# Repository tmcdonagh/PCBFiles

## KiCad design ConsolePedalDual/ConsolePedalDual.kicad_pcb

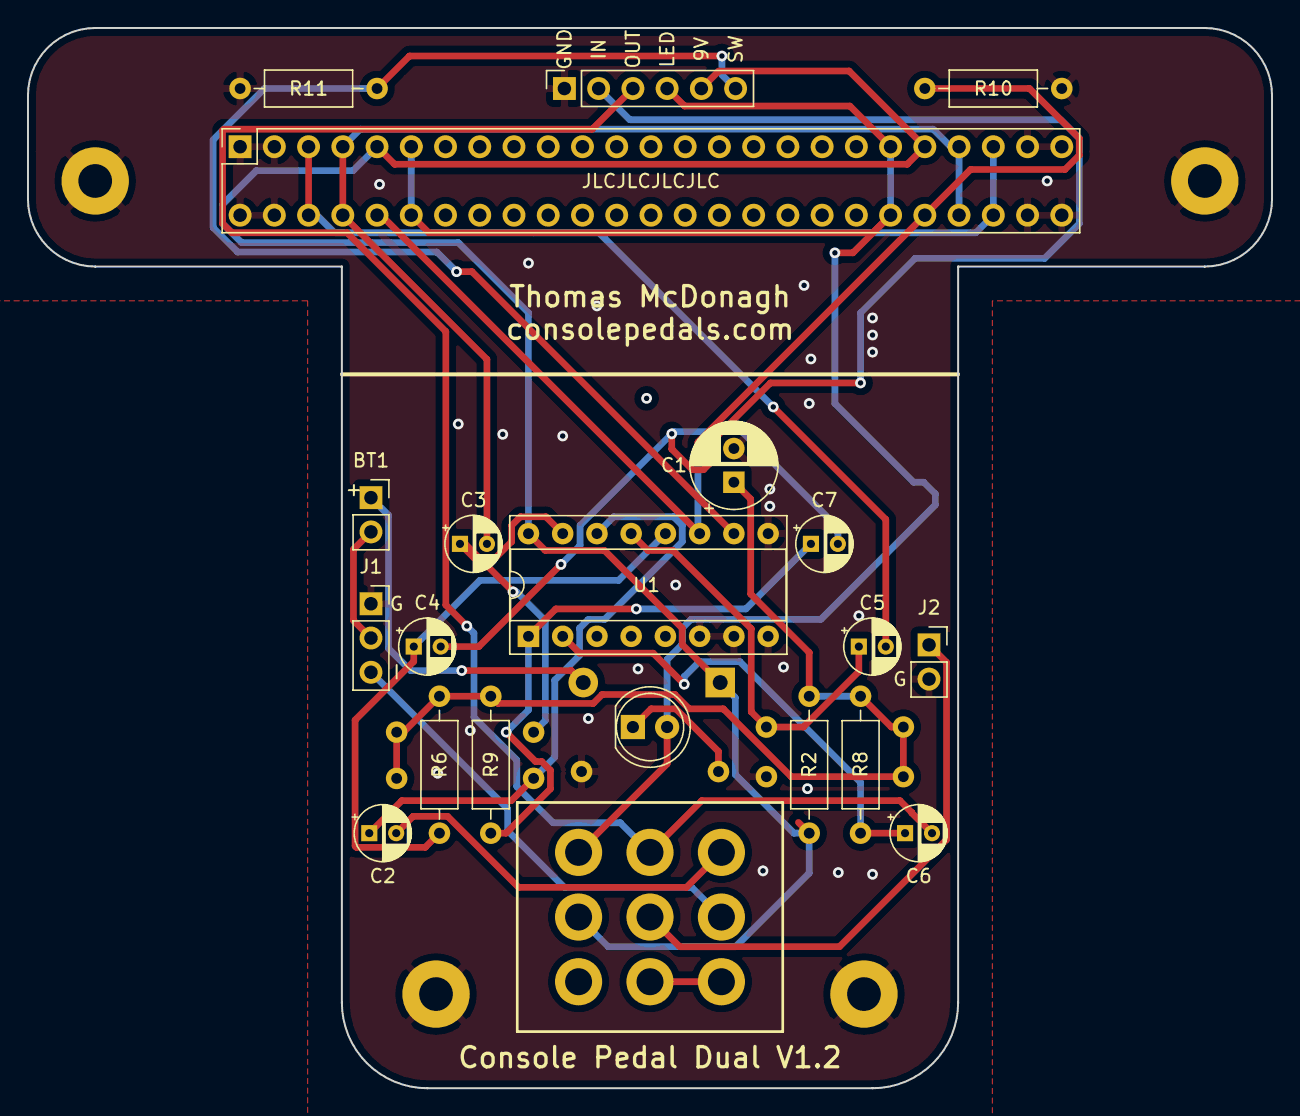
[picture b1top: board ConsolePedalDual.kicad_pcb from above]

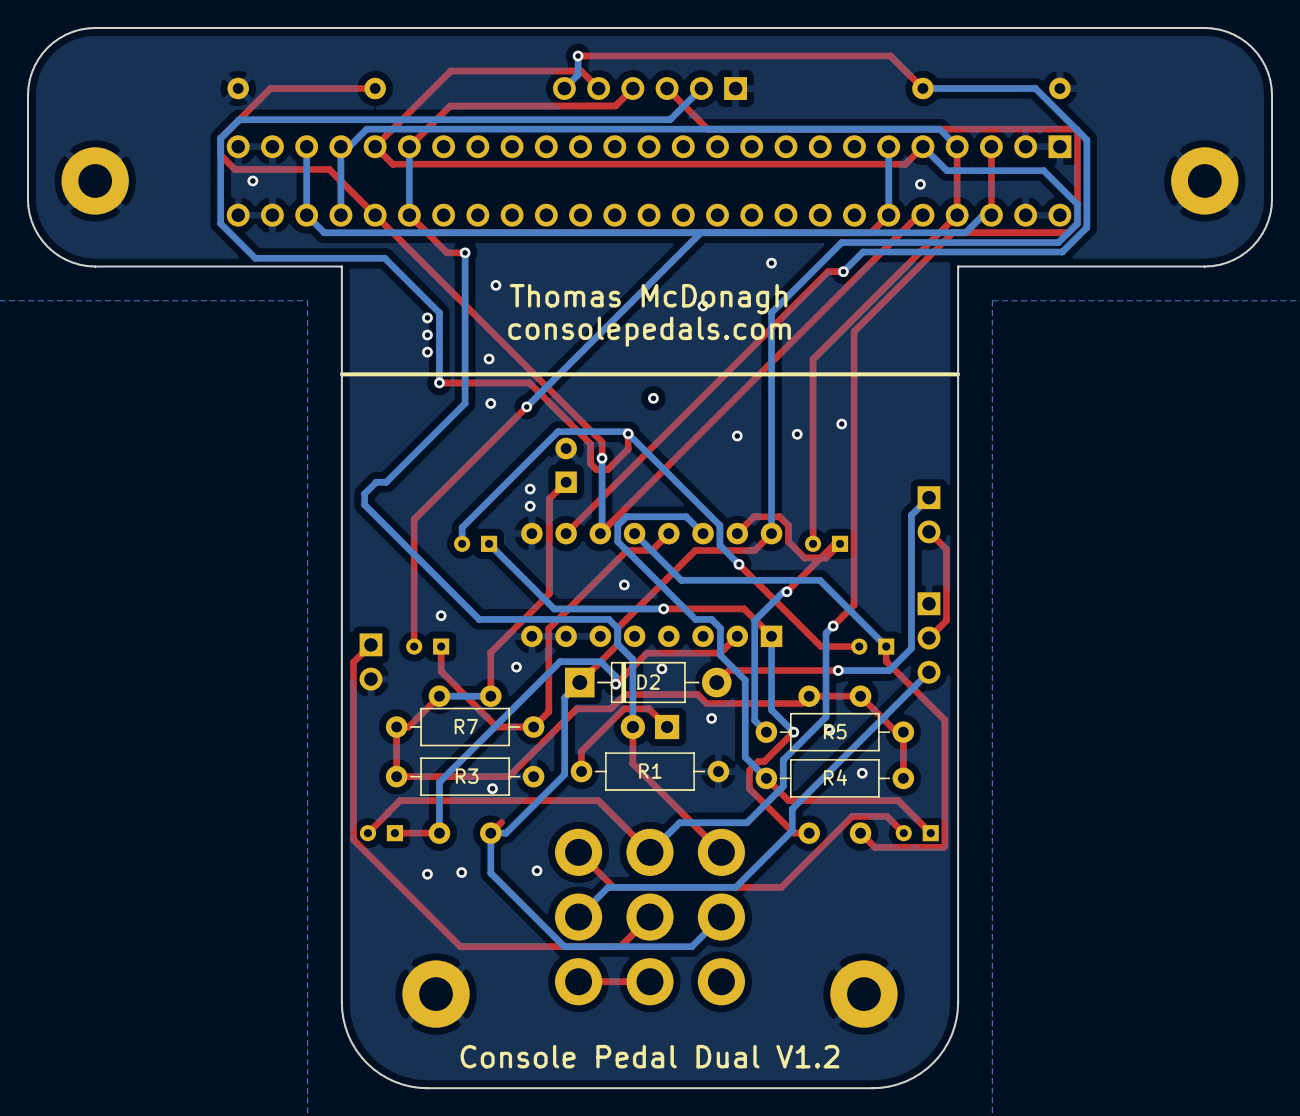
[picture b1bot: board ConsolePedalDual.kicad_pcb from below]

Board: 2 copper layers, 92.3 x 78.7 mm, 31 parts (6 on the bottom side), 23 nets.

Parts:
BT1: Battery; PinSocket_1x02_P2.54mm_Vertical
C1: 47uF; CP_Radial_D6.3mm_P2.50mm
C2, C3, C4, C5, C6, C7: 2.2uF; CP_Radial_D4.0mm_P2.00mm
D1: LED; LED_D5.0mm
D2: D; D_DO-41_SOD81_P10.16mm_Horizontal
H1, H2, H3, H4: Mount; MountingHole_2.5mm_Pad
J1: AudioJack3; PinSocket_1x03_P2.54mm_Vertical
J2: AudioJack2; PinSocket_1x02_P2.54mm_Vertical
J3: Slot A; n64Socket
J4: Slot B; PinSocket_1x06_P2.54mm_Vertical
R1: LED; R_Axial_DIN0207_L6.3mm_D2.5mm_P10.16mm_Horizontal
R2, R3: 10K; R_Axial_DIN0207_L6.3mm_D2.5mm_P10.16mm_Horizontal
R4, R5, R6, R7, R8, R9: 510K; R_Axial_DIN0207_L6.3mm_D2.5mm_P10.16mm_Horizontal
R10, R11: 3M; R_Axial_DIN0207_L6.3mm_D2.5mm_P10.16mm_Horizontal
S1: SWITCH-3PDT-PTH-STOMP; STOMP_SWITCH_3PDT
U1: CD4053B; DIP-16_W7.62mm_Socket

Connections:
+9V: D2.1, J3.9, J3.41, J4.5, R2.1, S1.P$8, U1.16
/Input: C2.2, S1.P$3
/LEDPower: D1.2, J3.11, J3.12, J3.39, J3.40, J4.4, S1.P$9
/Output: C6.2, J4.3, S1.P$6
/SlotA: J3.10, J3.42, R10.2, U1.11
/SlotAInput: C5.2, J3.5, J3.6, J3.45, J3.46
/SlotAOutput: C3.2, J3.7, J3.8, J3.43, J3.44
/SlotB: J4.6, R11.1, U1.10
/SlotBInput: C4.2, C7.2, J4.2
/VREF: C1.1, R2.2, R3.1, R4.2, R5.2, R6.1, R7.2, R8.1, R9.2
GND: C1.2, H1.1, H2.1, H3.1, H4.1, J1.1, J2.2, J3.1, J3.2, J3.3, J3.4, J3.47, J3.48, J3.49, J3.50, J4.1, R1.2, R3.2, R10.1, R11.2, U1.6, U1.7, U1.8, U1.9
unnamed: BT1.1, D2.2
unnamed: BT1.2, J1.2
unnamed: C2.1, R4.1, U1.14
unnamed: C3.1, R5.1, U1.15
unnamed: C4.1, R6.2, U1.12
unnamed: C5.1, R7.1, U1.13
unnamed: C6.1, R8.2, U1.2
unnamed: C7.1, R9.1, U1.1
unnamed: D1.1, R1.1
unnamed: J1.3, S1.P$2
unnamed: J2.1, S1.P$5
unnamed: S1.P$1, S1.P$4

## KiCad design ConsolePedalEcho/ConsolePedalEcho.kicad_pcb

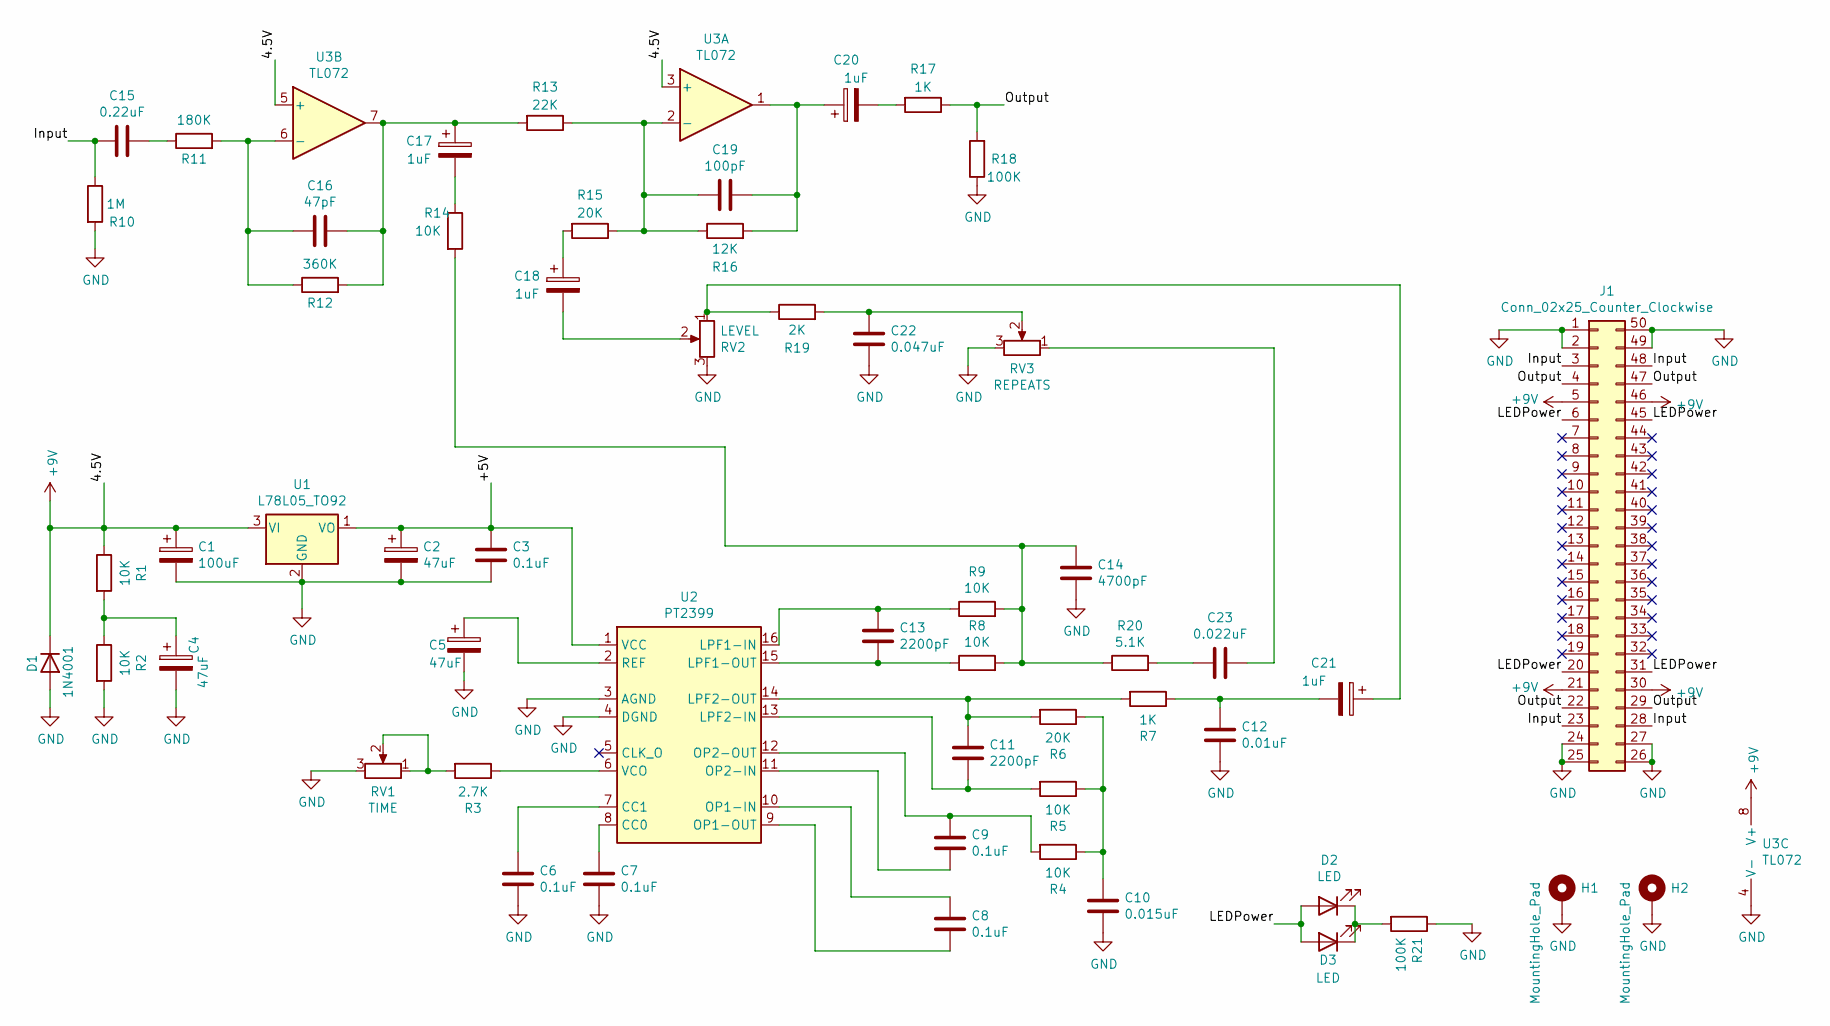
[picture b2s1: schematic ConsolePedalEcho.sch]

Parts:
C1: 100uF; CP_Radial_D8.0mm_P3.50mm
C2, C4, C5: 47uF; CP_Radial_D5.0mm_P2.00mm
C3, C6, C7, C8, C9: 0.1uF; C_Rect_L7.2mm_W2.5mm_P5.00mm_FKS2_FKP2_MKS2_MKP2
C10: 0.015uF; C_Rect_L7.2mm_W2.5mm_P5.00mm_FKS2_FKP2_MKS2_MKP2
C11, C13: 2200pF; C_Rect_L7.2mm_W2.5mm_P5.00mm_FKS2_FKP2_MKS2_MKP2
C12: 0.01uF; C_Rect_L7.2mm_W2.5mm_P5.00mm_FKS2_FKP2_MKS2_MKP2
C14: 4700pF; C_Rect_L7.2mm_W2.5mm_P5.00mm_FKS2_FKP2_MKS2_MKP2
C15: 0.22uF; C_Rect_L7.2mm_W2.5mm_P5.00mm_FKS2_FKP2_MKS2_MKP2
C16: 47pF; C_Axial_L3.8mm_D2.6mm_P7.50mm_Horizontal
C17, C18, C20, C21: 1uF; CP_Radial_D5.0mm_P2.00mm
C19: 100pF; C_Axial_L3.8mm_D2.6mm_P7.50mm_Horizontal
C22: 0.047uF; C_Rect_L7.2mm_W2.5mm_P5.00mm_FKS2_FKP2_MKS2_MKP2
C23: 0.022uF; C_Rect_L7.2mm_W2.5mm_P5.00mm_FKS2_FKP2_MKS2_MKP2
D1: 1N4001; D_DO-41_SOD81_P10.16mm_Horizontal
D2, D3: LED; LED_D5.0mm
H1, H2: MountingHole_Pad; MountingHole_2.5mm_Pad
J1: Conn_02x25_Counter_Clockwise; N64-Connector
R1, R2, R4, R5, R8, R9, R14: 10K; R_Axial_DIN0207_L6.3mm_D2.5mm_P10.16mm_Horizontal
R3: 2.7K; R_Axial_DIN0207_L6.3mm_D2.5mm_P10.16mm_Horizontal
R6, R15: 20K; R_Axial_DIN0207_L6.3mm_D2.5mm_P10.16mm_Horizontal
R7, R17: 1K; R_Axial_DIN0207_L6.3mm_D2.5mm_P10.16mm_Horizontal
R10: 1M; R_Axial_DIN0207_L6.3mm_D2.5mm_P10.16mm_Horizontal
R11: 180K; R_Axial_DIN0207_L6.3mm_D2.5mm_P10.16mm_Horizontal
R12: 360K; R_Axial_DIN0207_L6.3mm_D2.5mm_P10.16mm_Horizontal
R13: 22K; R_Axial_DIN0207_L6.3mm_D2.5mm_P10.16mm_Horizontal
R16: 12K; R_Axial_DIN0207_L6.3mm_D2.5mm_P10.16mm_Horizontal
R18, R21: 100K; R_Axial_DIN0207_L6.3mm_D2.5mm_P10.16mm_Horizontal
R19: 2K; R_Axial_DIN0207_L6.3mm_D2.5mm_P10.16mm_Horizontal
R20: 5.1K; R_Axial_DIN0207_L6.3mm_D2.5mm_P10.16mm_Horizontal
RV1: TIME; Potentiometer_Bourns_PTV09A-1_Single_Vertical
RV2: LEVEL; Potentiometer_Bourns_PTV09A-1_Single_Vertical
RV3: REPEATS; Potentiometer_Bourns_PTV09A-1_Single_Vertical
U1: L78L05_TO92; TO-92_Inline
U2: PT2399; DIP-16_W7.62mm_Socket
U3: TL072; DIP-8_W7.62mm_Socket

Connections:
+9V: C1.1, D1.1 (K), J1.5, J1.21, J1.30, J1.46, R1.1, U1.3 (VI), U3.3 (+), U3.5 (+), U3.8 (V+)
/+5V: C2.1, C3.1, U1.1 (VO), U2.1 (VCC)
/Input: C15.2, J1.3, J1.23, J1.28, J1.48, R10.1
/LEDPower: D2.2 (A), D3.2 (A), J1.6, J1.20, J1.31, J1.45
/Output: J1.4, J1.22, J1.29, J1.47, R17.1, R18.2
GND: C1.2, C2.2, C3.2, C4.2, C5.2, C6.2, C7.2, C10.2, C12.2, C14.2, C22.1, D1.2 (A), H1.1, H2.1, J1.1, J1.2, J1.24, J1.25, J1.26, J1.27, J1.49, J1.50, R2.2, R10.2, R18.1, R21.1, RV1.3, RV2.3, RV3.3, U1.2 (GND), U2.3 (AGND), U2.4 (DGND), U3.4 (V-)
unnamed: C4.1, R1.2, R2.1
unnamed: C5.1, U2.2 (REF)
unnamed: C6.1, U2.7 (CC1)
unnamed: C7.1, U2.8 (CC0)
unnamed: C8.1, U2.10 (OP1-IN)
unnamed: C8.2, U2.9 (OP1-OUT)
unnamed: C9.1, R4.2, U2.12 (OP2-OUT)
unnamed: C9.2, U2.11 (OP2-IN)
unnamed: C10.1, R4.1, R5.1, R6.1
unnamed: C11.1, R6.2, R7.2, U2.14 (LPF2-OUT)
unnamed: C11.2, R5.2, U2.13 (LPF2-IN)
unnamed: C12.1, C21.2, R7.1
unnamed: C13.1, R9.1, U2.16 (LPF1-IN)
unnamed: C13.2, R8.1, U2.15 (LPF1-OUT)
unnamed: C14.1, R8.2, R9.2, R14.2, R20.1
unnamed: C15.1, R11.1
unnamed: C16.1, C17.1, R12.2, R13.2, U3.7
unnamed: C16.2, R11.2, R12.1, U3.6 (-)
unnamed: C17.2, R14.1
unnamed: C18.1, R15.2
unnamed: C18.2, RV2.2
unnamed: C19.1, C20.1, R16.2, U3.1
unnamed: C19.2, R13.1, R15.1, R16.1, U3.2 (-)
unnamed: C20.2, R17.2
unnamed: C21.1, R19.1, RV2.1
unnamed: C22.2, R19.2, RV3.2
unnamed: C23.1, R20.2
unnamed: C23.2, RV3.1
unnamed: D2.1 (K), D3.1 (K), R21.2
unnamed: R3.1, U2.6 (VCO)
unnamed: R3.2, RV1.1, RV1.2

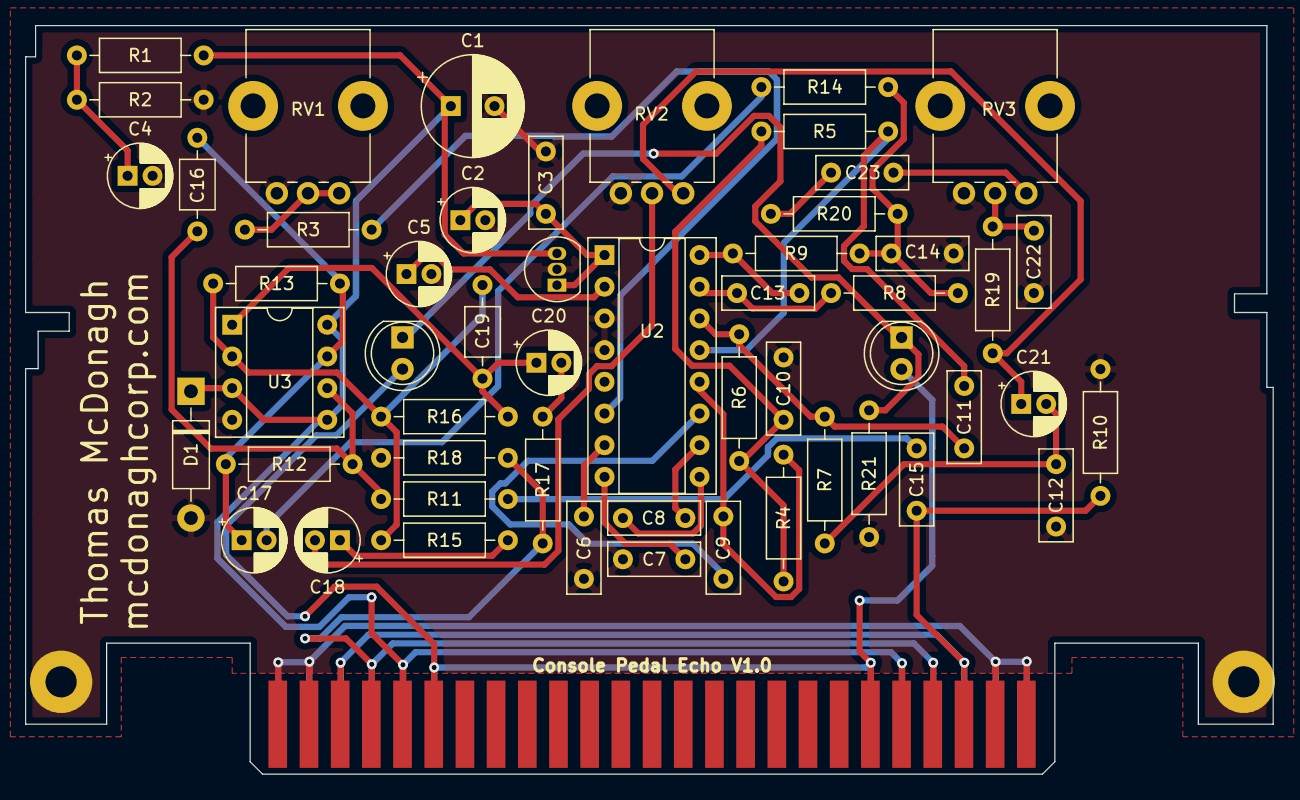
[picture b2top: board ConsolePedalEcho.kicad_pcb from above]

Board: 2 copper layers, 100.0 x 60.0 mm, 56 parts (0 on the bottom side), 37 nets.

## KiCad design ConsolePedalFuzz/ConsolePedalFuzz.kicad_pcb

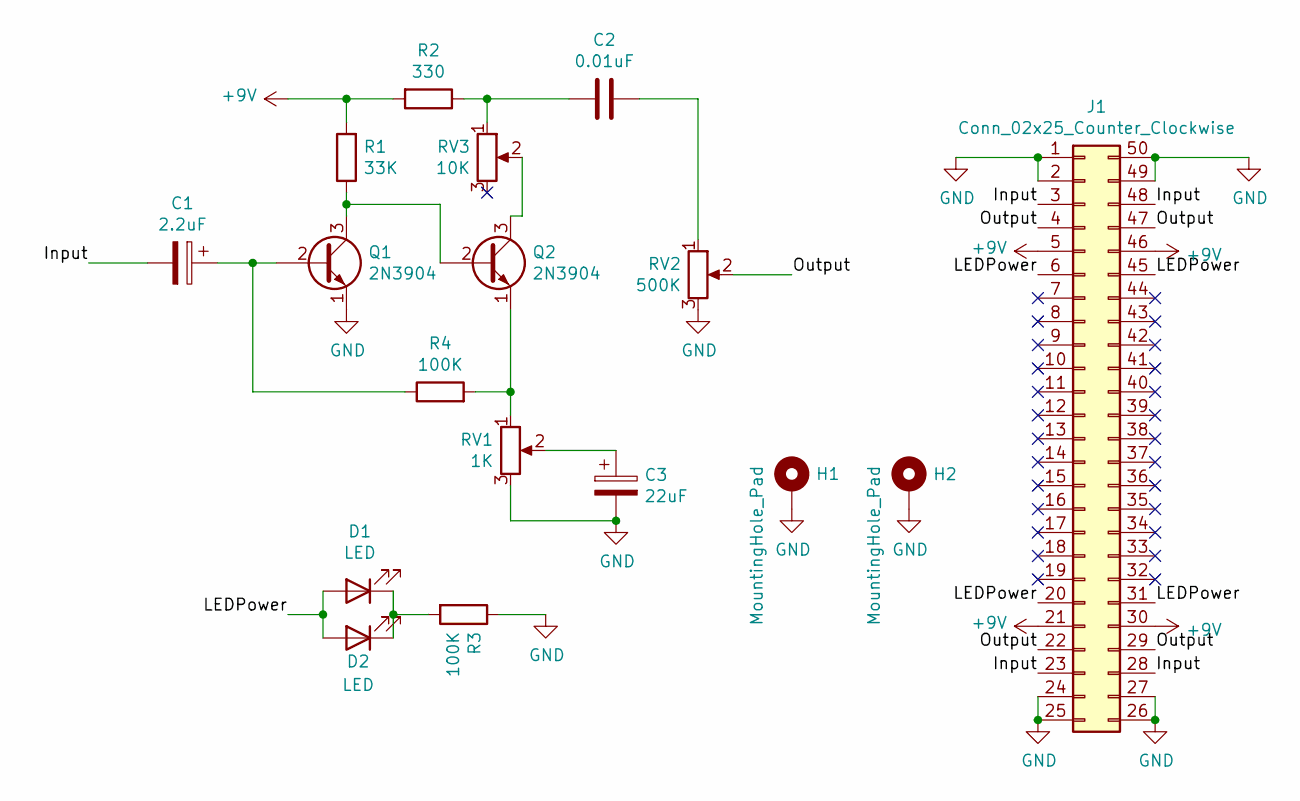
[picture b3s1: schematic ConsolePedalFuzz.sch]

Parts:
C1: 2.2uF; CP_Axial_L11.0mm_D5.0mm_P18.00mm_Horizontal
C2: 0.01uF; C_Disc_D10.5mm_W5.0mm_P7.50mm
C3: 22uF; CP_Axial_L11.0mm_D6.0mm_P18.00mm_Horizontal
D1, D2: LED; LED_D5.0mm
H1, H2: MountingHole_Pad; MountingHole_2.5mm_Pad
J1: Conn_02x25_Counter_Clockwise; N64-Connector
Q1, Q2: 2N3904; TO-92_Inline
R1: 33K; R_Axial_DIN0207_L6.3mm_D2.5mm_P10.16mm_Horizontal
R2: 330; R_Axial_DIN0207_L6.3mm_D2.5mm_P10.16mm_Horizontal
R3, R4: 100K; R_Axial_DIN0207_L6.3mm_D2.5mm_P10.16mm_Horizontal
RV1: 1K; Potentiometer_Bourns_PTV09A-1_Single_Vertical
RV2: 500K; Potentiometer_Bourns_PTV09A-1_Single_Vertical
RV3: 10K; Potentiometer_Bourns_3386F_Vertical

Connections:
+9V: J1.5, J1.21, J1.30, J1.46, R1.2, R2.2
/Input: C1.2, J1.3, J1.23, J1.28, J1.48
/LEDPower: D1.2 (A), D2.2 (A), J1.6, J1.20, J1.31, J1.45
/Output: J1.4, J1.22, J1.29, J1.47, RV2.2
GND: C3.2, H1.1, H2.1, J1.1, J1.2, J1.24, J1.25, J1.26, J1.27, J1.49, J1.50, Q1.1 (E), R3.1, RV1.3, RV2.3
unnamed: C1.1, Q1.2 (B), R4.1
unnamed: C2.1, RV2.1
unnamed: C2.2, R2.1, RV3.1
unnamed: C3.1, RV1.2
unnamed: D1.1 (K), D2.1 (K), R3.2
unnamed: Q1.3 (C), Q2.2 (B), R1.1
unnamed: Q2.1 (E), R4.2, RV1.1
unnamed: Q2.3 (C), RV3.2

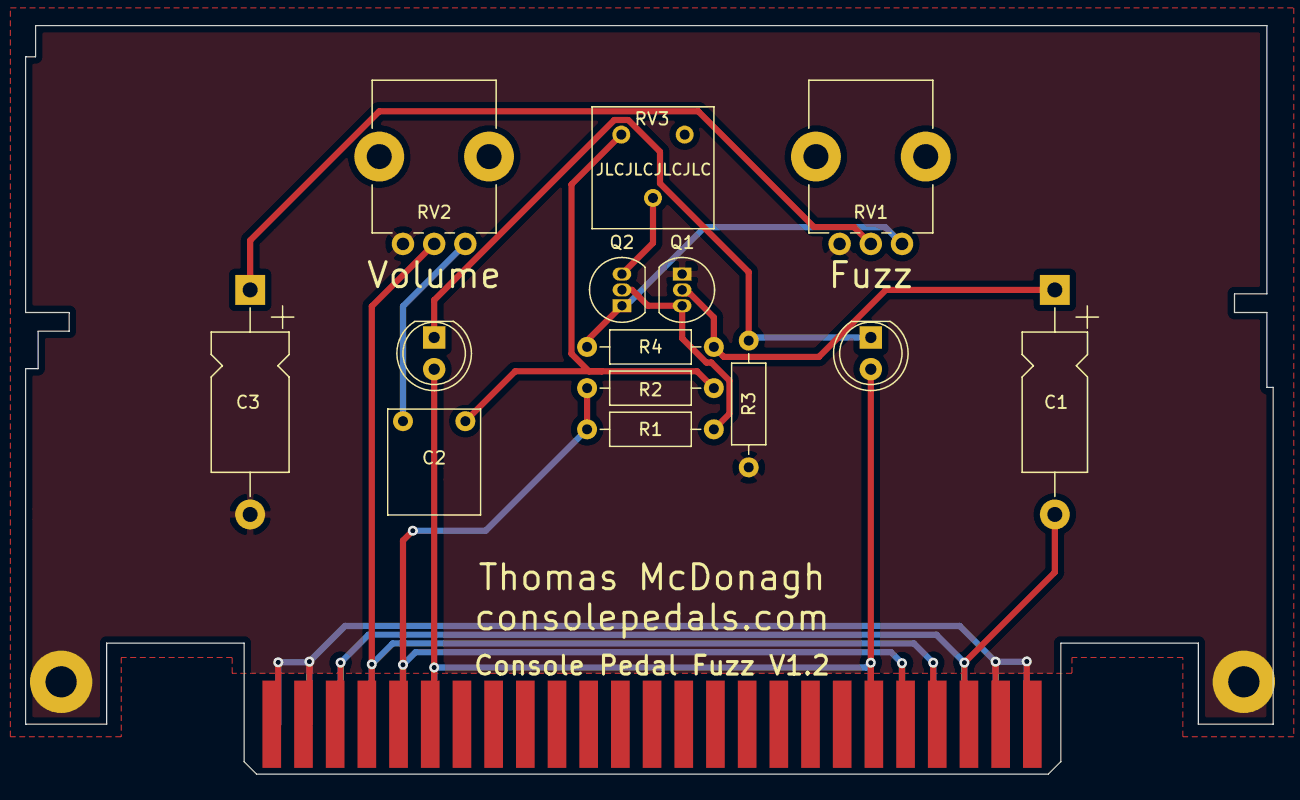
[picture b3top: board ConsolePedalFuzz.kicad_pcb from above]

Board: 2 copper layers, 100.0 x 60.0 mm, 17 parts (0 on the bottom side), 13 nets.

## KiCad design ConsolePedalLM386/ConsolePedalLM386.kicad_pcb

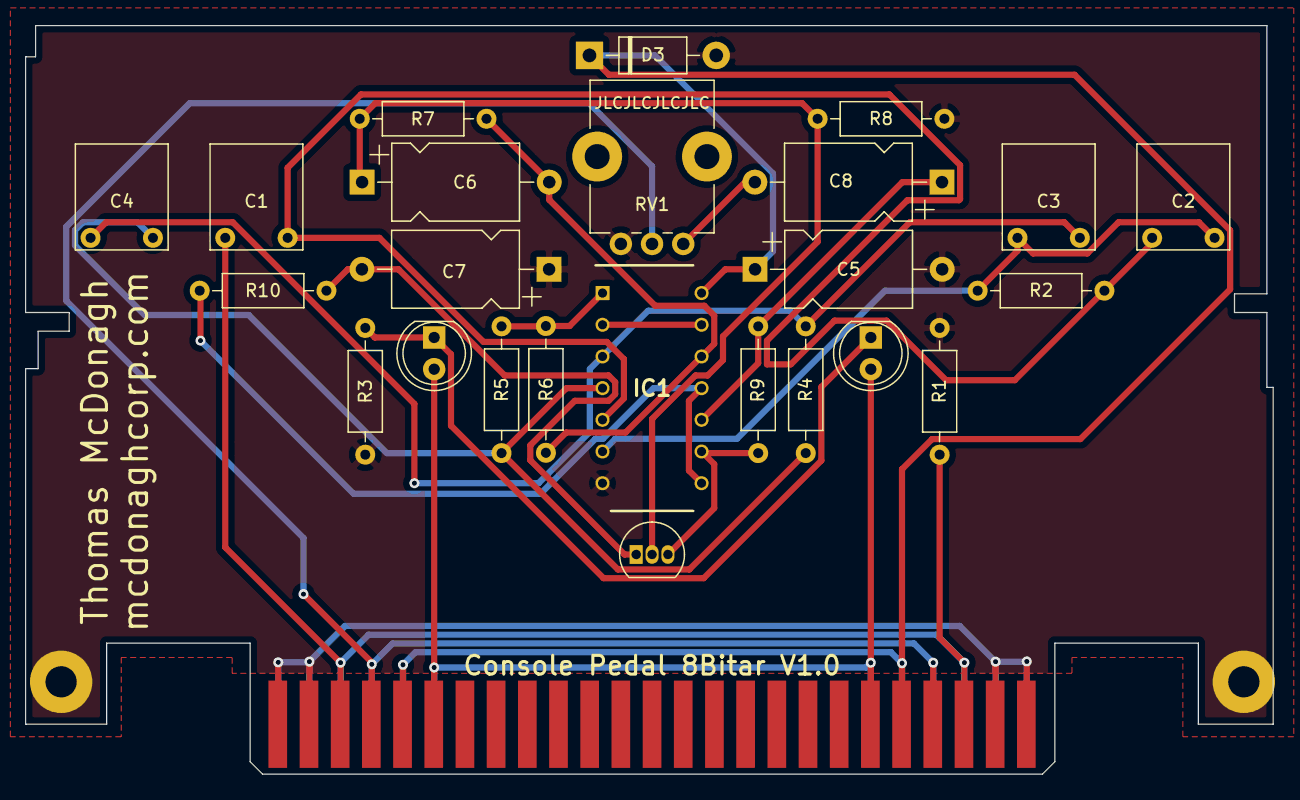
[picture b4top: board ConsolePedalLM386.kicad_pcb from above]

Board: 2 copper layers, 100.0 x 60.0 mm, 27 parts (0 on the bottom side), 19 nets.

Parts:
C1, C3: 0.1uF; C_Flat_L7.2_H6.5
C2: 2200pF; C_Flat_L7.2_H6.5
C4: 4700pF; C_Flat_L7.2_H6.5
C5, C8: 10uF; CP_Axial_L10.0mm_D6.0mm_P15.00mm_Horizontal
C6: 100pF; CP_Axial_L10.0mm_D6.0mm_P15.00mm_Horizontal
C7: 1000pF; CP_Axial_L10.0mm_D6.0mm_P15.00mm_Horizontal
D1, D2: LED; LED_D5.0mm
D3: 1N4001; D_DO-41_SOD81_P10.16mm_Horizontal
H1, H2: MountingHole_Pad; MountingHole_2.5mm_Pad
IC1: CD4069UBE; DIP794W53P254L1930H508Q14N
J1: Conn_02x25_Counter_Clockwise; N64-Connector
Q1: 2N3904; TO-92_Inline
R1, R2, R4, R6: 1M; R_Axial_DIN0207_L6.3mm_D2.5mm_P10.16mm_Horizontal
R3, R10: 100K; R_Axial_DIN0207_L6.3mm_D2.5mm_P10.16mm_Horizontal
R5: 47K; R_Axial_DIN0207_L6.3mm_D2.5mm_P10.16mm_Horizontal
R7, R8, R9: 10K; R_Axial_DIN0207_L6.3mm_D2.5mm_P10.16mm_Horizontal
RV1: A10K; Potentiometer_Bourns_PTV09A-1_Single_Vertical

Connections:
+9V: C5.1, D3.1, IC1.14, J1.5, J1.21, J1.30, J1.46
/Input: C1.2, J1.3, J1.23, J1.28, J1.48, R1.1
/LEDPower: D1.2, D2.2, J1.6, J1.20, J1.31, J1.45
/Output: J1.4, J1.22, J1.29, J1.47, RV1.2
/pin1: IC1.1, R5.1, R6.2
/pin3: C3.1, C4.2, IC1.3, R4.2
/pin4: C4.1, IC1.4, R4.1, R5.2
/pin5: C1.1, C2.2, IC1.5, R2.2
/pin6: C2.1, C3.2, IC1.6, R2.1
/pin9: IC1.9, Q1.3, R9.2
/pin10: C8.1, IC1.10, R9.1
/pin11: IC1.8, IC1.11, R10.2
/pin12: C6.2, IC1.12, R6.1, R7.1
/pin13: IC1.2, IC1.13
GND: C5.2, C7.1, D3.2, H1.1, H2.1, IC1.7, J1.1, J1.2, J1.24, J1.25, J1.26, J1.27, J1.49, J1.50, R1.2, R3.1, R8.2, RV1.3
unnamed: C6.1, Q1.2, R7.2, R8.1
unnamed: C7.2, Q1.1, R10.1
unnamed: C8.2, RV1.1
unnamed: D1.1, D2.1, R3.2

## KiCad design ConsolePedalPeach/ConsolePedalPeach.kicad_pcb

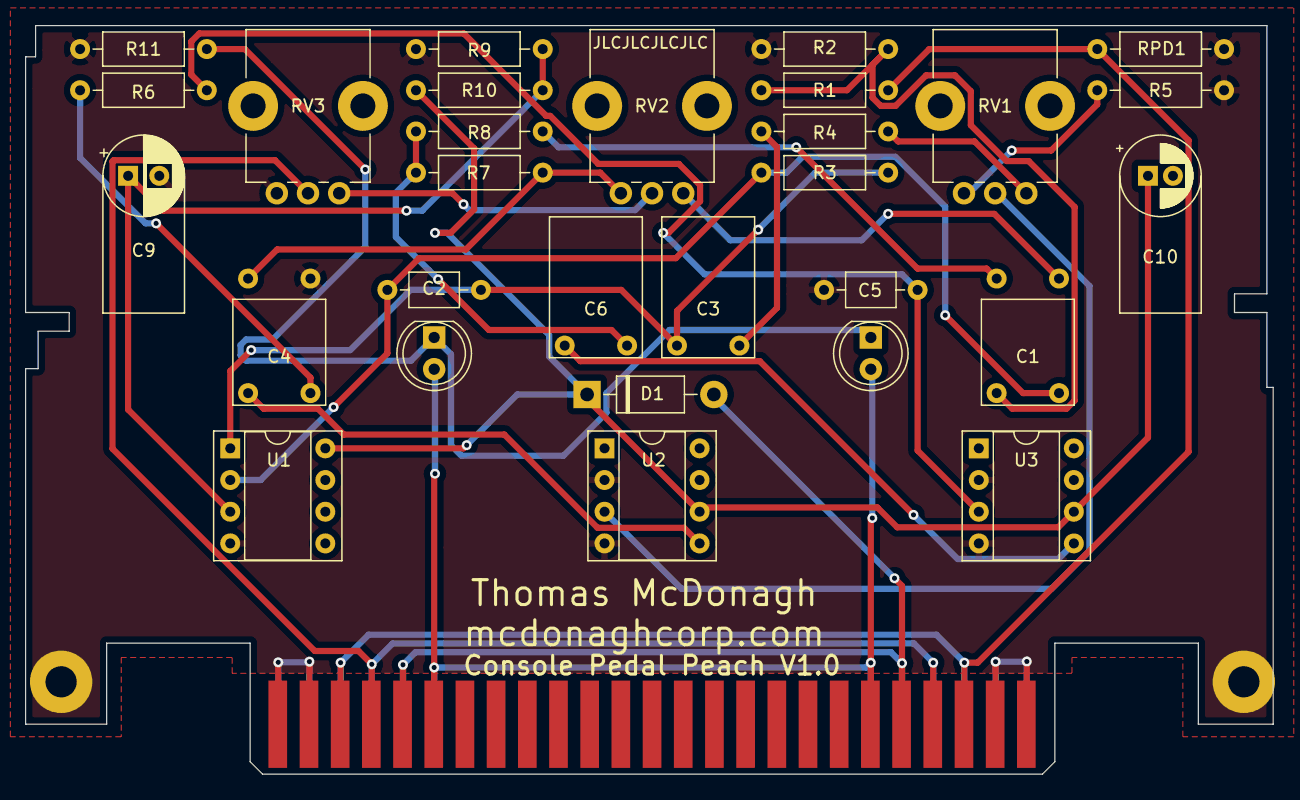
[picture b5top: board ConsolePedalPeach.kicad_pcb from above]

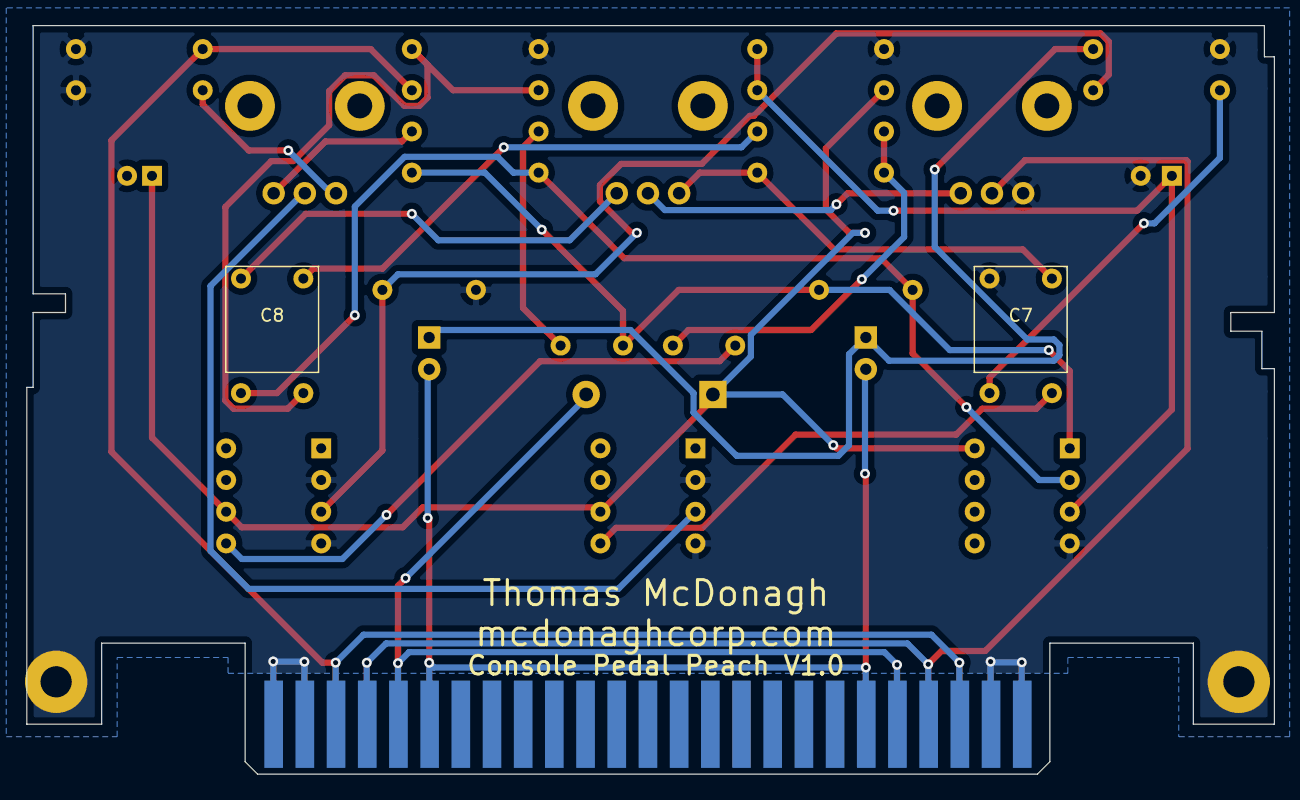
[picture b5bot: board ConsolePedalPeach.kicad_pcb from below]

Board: 2 copper layers, 100.0 x 60.0 mm, 34 parts (2 on the bottom side), 24 nets.

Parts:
C1, C4: 100nF; C_Flat_L7.2_H6.5
C2: 100pF; C_Axial_L3.8mm_D2.6mm_P7.50mm_Horizontal
C3, C6: 1uF; C_Flat_L7.2_H10
C5: 18pF; C_Axial_L3.8mm_D2.6mm_P7.50mm_Horizontal
C7: 470nF; C_Flat_L7.2_H6.5
C8: 10nF; C_Flat_L7.2_H6.5
C9: 10uF; CP_Radial_D6.3mm_P2.50mm_L11.0mm
C10: 100uF; CP_Radial_D6.3mm_P2.00mm_L11.0mm
D1: 1N5817; D_DO-41_SOD81_P10.16mm_Horizontal
D2, D3: LED; LED_D5.0mm
H1, H2: MountingHole_Pad; MountingHole_2.5mm_Pad
J1: Conn_02x25_Counter_Clockwise; N64-Connector
R1, R9, R10: 33K; R_Axial_DIN0207_L6.3mm_D2.5mm_P10.16mm_Horizontal
R2, R11: 100K; R_Axial_DIN0207_L6.3mm_D2.5mm_P10.16mm_Horizontal
R3: 560K; R_Axial_DIN0207_L6.3mm_D2.5mm_P10.16mm_Horizontal
R4: 9.1K; R_Axial_DIN0207_L6.3mm_D2.5mm_P10.16mm_Horizontal
R5: 100; R_Axial_DIN0207_L6.3mm_D2.5mm_P10.16mm_Horizontal
R6: 120K; R_Axial_DIN0207_L6.3mm_D2.5mm_P10.16mm_Horizontal
R7: 10K; R_Axial_DIN0207_L6.3mm_D2.5mm_P10.16mm_Horizontal
R8: 39K; R_Axial_DIN0207_L6.3mm_D2.5mm_P10.16mm_Horizontal
RPD1: 1M; R_Axial_DIN0207_L6.3mm_D2.5mm_P10.16mm_Horizontal
RV1: 10KA Fuzz; Potentiometer_Bourns_PTV09A-1_Single_Vertical
RV2: 10KB Tone; Potentiometer_Bourns_PTV09A-1_Single_Vertical
RV3: 100KB Volume; Potentiometer_Bourns_PTV09A-1_Single_Vertical
U1: TL072; DIP-8_W7.62mm_Socket
U2, U3: LM386; DIP-8_W7.62mm_Socket

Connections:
+9V: D1.2, J1.5, J1.21, J1.30, J1.46
/9V: C10.1, D1.1, R10.2, U1.8, U2.6, U3.6
/Input: J1.3, J1.23, J1.28, J1.48, R1.2, RPD1.2
/LEDPower: D2.2, D3.2, J1.6, J1.20, J1.31, J1.45
/Output: J1.4, J1.22, J1.29, J1.47, RV3.2
/VR: C9.1, R9.2, R10.1, U1.3
GND: C5.2, C7.1, C9.2, C10.2, H1.1, H2.1, J1.1, J1.2, J1.24, J1.25, J1.26, J1.27, J1.49, J1.50, R2.1, R5.2, R9.1, R11.1, RPD1.1, RV3.3, U1.4, U2.2, U2.4, U3.2, U3.4
unnamed: C1.1, C2.1, R3.1, U1.2
unnamed: C1.2, R1.1, R2.2
unnamed: C2.2, C3.2, R3.2, U1.1
unnamed: C3.1, R4.2
unnamed: C4.1, R6.2
unnamed: C4.2, U2.5
unnamed: C5.1, R6.1, U3.3
unnamed: C6.1, R7.1, R8.2
unnamed: C6.2, U3.5
unnamed: C7.2, R7.2, RV2.3
unnamed: C8.1, RV2.1
unnamed: C8.2, R8.1
unnamed: D2.1, D3.1, R11.2
unnamed: R4.1, RV1.1
unnamed: R5.1, RV1.3
unnamed: RV1.2, U2.3
unnamed: RV2.2, RV3.1

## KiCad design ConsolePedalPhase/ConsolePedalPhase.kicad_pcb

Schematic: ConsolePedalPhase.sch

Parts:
C1, C4, C6, C7, C16, C19: 100nF; C_0603_1608Metric
C2: 22nF; C_0603_1608Metric
C3, C8, C14: 10nF; C_0603_1608Metric
C5, C10: 100uF; C_0603_1608Metric
C9: 220nF; C_0603_1608Metric
C11: 10uF; C_0603_1608Metric
C12: 2.2nF; C_0603_1608Metric
C13: 1nF; C_0603_1608Metric
C15: 470pF; C_0603_1608Metric
C17: 4.7nF; C_0603_1608Metric
C18: 33nF; C_0603_1608Metric
D1, D2: LED; LED_D5.0mm
D3: 1N5817; D_SOD-123
J1: Conn_02x25_Counter_Clockwise; N64-Connector
J2: AudioJack2; Jack_3.5mm_CUI_SJ1-3535NG_Horizontal
R1, R2: 1M; R_0603_1608Metric
R3, R4, R5, R8, R9, R17, R20, R23: 100K; R_0603_1608Metric
R6, R11, R12, R22, R24, R25: 10K; R_0603_1608Metric
R7, R18: 4.7K; R_0603_1608Metric
R10: 470K; R_0603_1608Metric
R13, R14: 22K; R_0603_1608Metric
R15, R16, R21: 330K; R_0603_1608Metric
R19: 39K; R_0603_1608Metric
RV1: 20K; Potentiometer_Alps_RK09L_Single_Vertical
RV2: C100K; Potentiometer_Alps_RK09L_Single_Vertical
RV3: 1M; Potentiometer_Alps_RK09L_Single_Vertical
SW1: SW_DPDT_x2; DPDTSwitch
U1: TL072; SOIC-8_3.9x4.9mm_P1.27mm
U2: TL074; SOIC-14_3.9x8.7mm_P1.27mm
U3: CD4046BE; SOP-16_3.9x9.9mm_P1.27mm

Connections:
+9V: C5.1, C6.2, D3.1 (K), J1.5, J1.21, J1.30, J1.46, R11.1, U1.8 (V+), U2.4 (V+), U3.16
/Input: C1.2, J1.3, J1.23, J1.28, J1.48, R1.1
/LEDPower: D1.2 (A), D2.2 (A), J1.6, J1.20, J1.31, J1.45
/Output: C16.2, J1.4, J1.22, J1.29, J1.47, R23.1
CHIP1: C4.2, R17.2, U1.1, U1.2 (-)
COMP_IN: RV1.3, U3.3
GND: C3.1, C5.2, C6.1, C8.1, C10.2, C13.2, C17.1, C19.1, D3.2 (A), J1.1, J1.2, J1.24, J1.25, J1.26, J1.27, J1.49, J1.50, J2.S, R1.2, R3.1, R12.2, R23.2, R24.1, RV3.1, SW1.1 (A), SW1.3 (C), SW1.5 (B), U1.4 (V-), U2.11 (V-), U3.5, U3.8; also elsewhere on the board
unnamed: C1.1, R2.1, U1.3 (+)
unnamed: C2.1, SW1.2 (B)
unnamed: C4.1, R6.2, R7.2
unnamed: C7.2, R8.1, R9.1, R14.2
unnamed: C8.2, R13.1, R15.2
unnamed: C9.2, C11.1, R14.1
unnamed: C11.2, RV2.1
unnamed: C12.1, R15.1, R16.2
unnamed: C12.2, R19.2, U2.6 (-), U2.7, U2.12 (+)
unnamed: C13.1, R16.1, U2.5 (+)
unnamed: C14.1, R21.2
unnamed: C14.2, R19.1, U2.13 (-)
unnamed: C15.1, R17.1, R18.1, R20.1, U1.6 (-)
unnamed: C15.2, C16.1, R20.2, U1.7
unnamed: C18.1, U3.7
unnamed: C18.2, U3.6
unnamed: C19.2, J2.T, R25.1
unnamed: D1.1 (K), D2.1 (K), R3.2
unnamed: R4.1, R8.2, SW1.6 (C)
unnamed: R5.1, R9.2, SW1.4 (A)
unnamed: R6.1, R10.1, U2.2 (-)
unnamed: R10.2, R13.2, U2.1
unnamed: R18.2, RV2.2, RV2.3
unnamed: R21.1, RV3.2, RV3.3
unnamed: R22.2, U2.14
unnamed: R24.2, U3.11
unnamed: U2.8, U2.9 (-)
PH_COMP2_OUT: R25.2, U3.9, U3.13
PH_PULSE: R5.2, U3.1
SIG_IN: C17.2, R22.1, U3.14
VCC: C7.1, C9.1, C10.1, R2.2, R7.1, R11.2, R12.1, U1.5 (+), U2.3 (+), U2.10 (+)
VCO_OUT: C2.2, C3.2, R4.2, RV1.1, RV1.2, U3.4

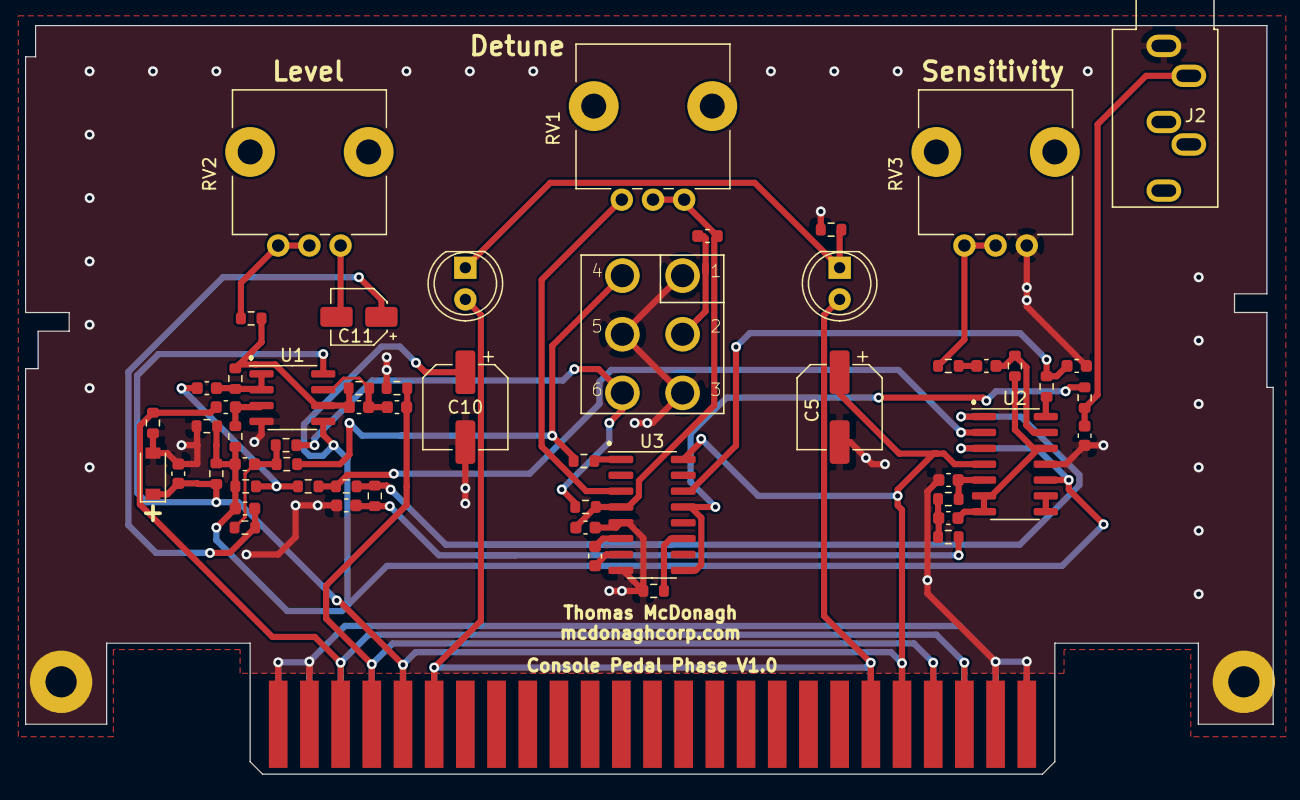
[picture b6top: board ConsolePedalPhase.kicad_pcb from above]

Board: 2 copper layers, 100.0 x 60.0 mm, 58 parts (0 on the bottom side), 39 nets.

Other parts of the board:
H1, H2: MountingHole_Pad; MountingHole_2.5mm_Pad

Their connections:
GND: H1.1, H2.1; also elsewhere on the board

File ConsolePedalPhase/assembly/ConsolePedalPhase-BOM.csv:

Value,Designator,Footprint,LCSC Part #,
100nF,"C1,C4,C6,C7,C16,C19",0603,C14663,
10uF,C11,SMD-ECAP-4x5.3,C134721,
2.2nF,C12,0603,C1604,
1nF,C13,0603,C1588,
470pF,C15,0603,C1620,
4.7nF,C17,0603,C53987,
33nF,C18,0603,C21117,
22nF,C2,0603,C21122,
100uF,"C5,C10",SMD-ECAP-6.3x5.3,C134723,
10nF,"C3,C8,C14",0603,C57112,
220nF,C9,0603,C21120,
1N5817,D3,SOD-123,C727113,
1M,"R1,R2",0603,C22935,
470K,R10,0603,C23178,
22K,"R13,R14",0603,C31850,
330K,"R15,R16,R21",0603,C23137,
39K,R19,0603,C23153,
100K,"R3,R4,R5,R8,R9,R17,R20,R23",0603,C25803,
10K,"R6,R11,R12,R22,R24,R25",0603,C25804,
4.7K,"R7,R18",0603,C23162,
TL072,U1,SOIC-8_3.9x4.9x1.27P,C6961,
TL074,U2,SOIC-14_3.9x8.7x1.27P,C12594,
CD4046BE,U3,SOIC-16_3.9x9.9x1.27P,C6542,
,,,,
,,,,
,,,,
,,,,
